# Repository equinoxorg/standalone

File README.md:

#Standalone Designs

##Hardware
This project includes hardware schematics and board layouts for the standalone batterbox (izuba.box) for e.quinox (www.e.quinox.org).

Cadsoft EAGLE is the tool of choice when designing PCBs

###Contents

The following designs are included in this repository

* [Stand_Alone] : The main PCB board controlling payment and outputs
* [Stand_Alone_Inv_Adapter] : The adapter board used in the commercial unit, allows high power loads such as the inverter to be switched. Also provided 2 extra USB outputs and fan contol. Connects the the main boards inverter adapter connector.

##Software

This project includes PIC microcontroller software for the standalone batterbox (izuba.box) for e.quinox (www.e.quinox.org).

The project is MPLAB v1.20. The compiler is the Hi-Tech PIC18 v9.80 Lite C compiler

###Contents

The following designs are included in this repository

* [Stand_Alone] : The main firmware for the standalone units

###Notes
The unlock_code.c file has been deliberatly exluded as it would allow misuse of the payment system. If this is a problem please contact e.quinox.org

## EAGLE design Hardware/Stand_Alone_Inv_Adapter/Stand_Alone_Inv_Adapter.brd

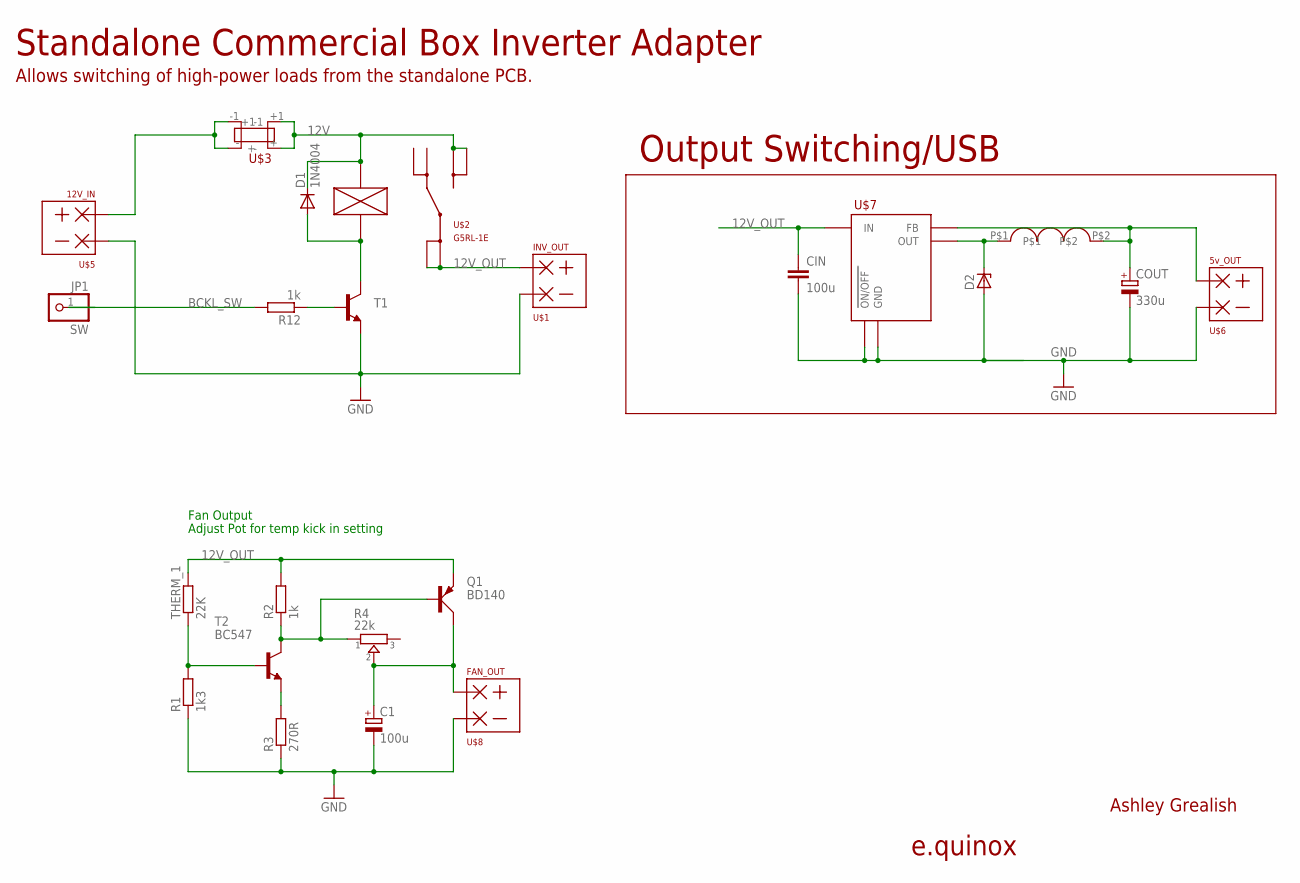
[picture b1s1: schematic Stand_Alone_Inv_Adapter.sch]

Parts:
C1: 100u; B45181B
CIN: 100u; C2.5-2
COUT: 330u; B45181D
D1: 1N4004; DO41-10
D2: ZENER-DIODEDO41Z10; DO41Z10
JP1: SW; 1X01
Q1: BD140; TO126AV
R1: 1k3; 0207/10
R2: 1k; 0207/10
R3: 270R; 0207/10
R4: 22k; TRIMMER_3362P
R12: 1k; RTH025W
T1: BC546-NPN-TO92-CBE; TO92-CBE
T2: BC547; TO92
THERM_1: 22K; 0204/7
U$1: INV_OUT; TERMINAL_2WAY
U$2: G5RL-1E
U$3: EQBX_FUSEEQBX_FUSE; EQBX_FUSE
U$4: EQBX_INDUCTOR2; INDUCTOR
U$5: 12V_IN; TERMINAL_2WAY
U$6: 5v_OUT; TERMINAL_2WAY
U$7: LM2575; TO220-5
U$8: FAN_OUT; TERMINAL_2WAY

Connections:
12V: D1.C, U$2.COIL+, U$2.NO@1 (NO), U$2.NO@2 (NO), U$3.+, U$3.+1
12V_OUT: CIN.1, Q1.E, R2.2, THERM_1.2, U$1.P$1, U$2.COM@1 (COM), U$2.COM@2 (COM), U$7.P$1 (IN)
BCKL_SW: JP1.1, R12.2
GND: C1.-, CIN.2, COUT.-, D2.A, R1.1, R3.1, T1.E, U$1.P$2, U$5.P$2, U$6.P$2, U$7.P$3 (GND), U$7.P$5 (ON/OFF), U$8.P$2
unnamed: D1.A, T1.C, U$2.COIL-
unnamed: R12.1, T1.B
unnamed: U$3.-, U$3.-1, U$5.P$1
unnamed: R1.2, T2.2 (B), THERM_1.1
unnamed: Q1.B, R2.1, R4.1, T2.3 (C)
unnamed: R3.2, T2.1 (E)
unnamed: C1.+, Q1.C, R4.2, U$8.P$1
unnamed: COUT.+, U$4.P$2, U$6.P$1, U$7.P$4 (FB)
unnamed: D2.C, U$4.P$1, U$7.P$2 (OUT)

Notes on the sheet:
e.quinox
Ashley Grealish
Standalone Commercial Box Inverter Adapter
Allows switching of high-power loads from the standalone PCB.
Output Switching/USB
Fan Output
Adjust Pot for temp kick in setting

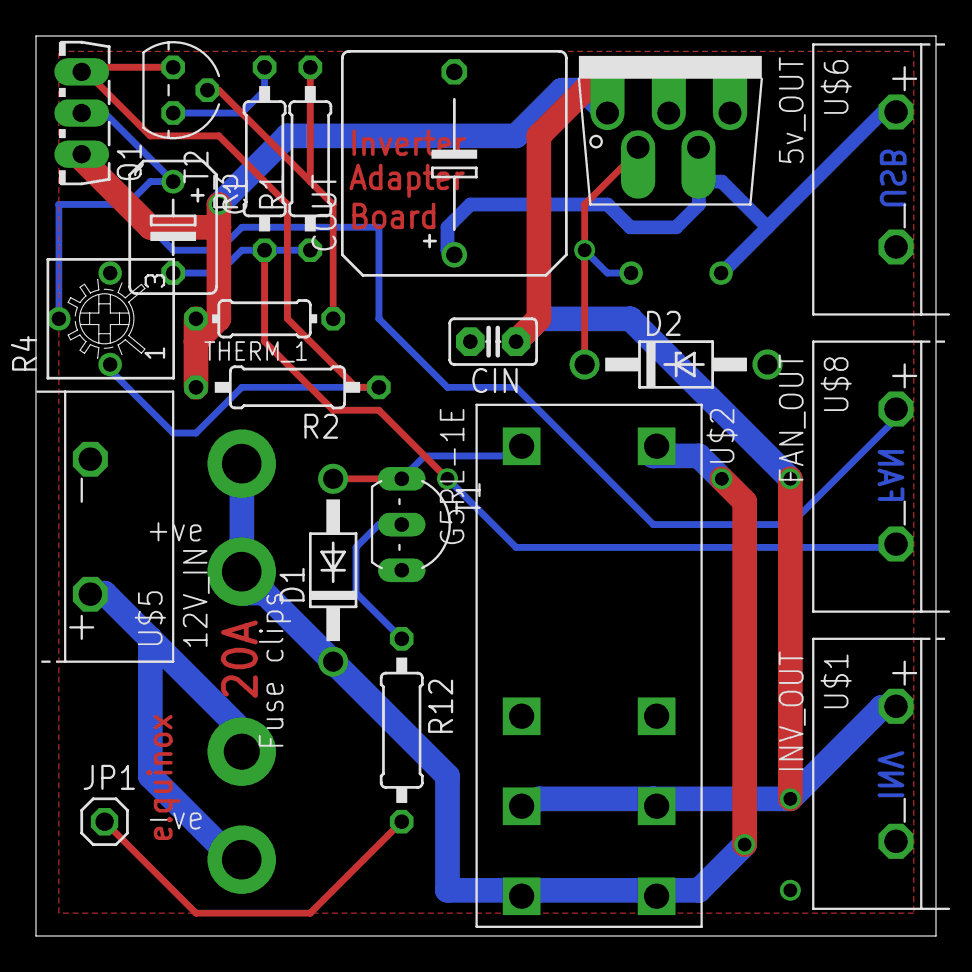
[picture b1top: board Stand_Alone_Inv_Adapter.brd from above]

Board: 2 copper layers, 50.0 x 50.0 mm, 23 parts (0 on the bottom side), 13 nets.

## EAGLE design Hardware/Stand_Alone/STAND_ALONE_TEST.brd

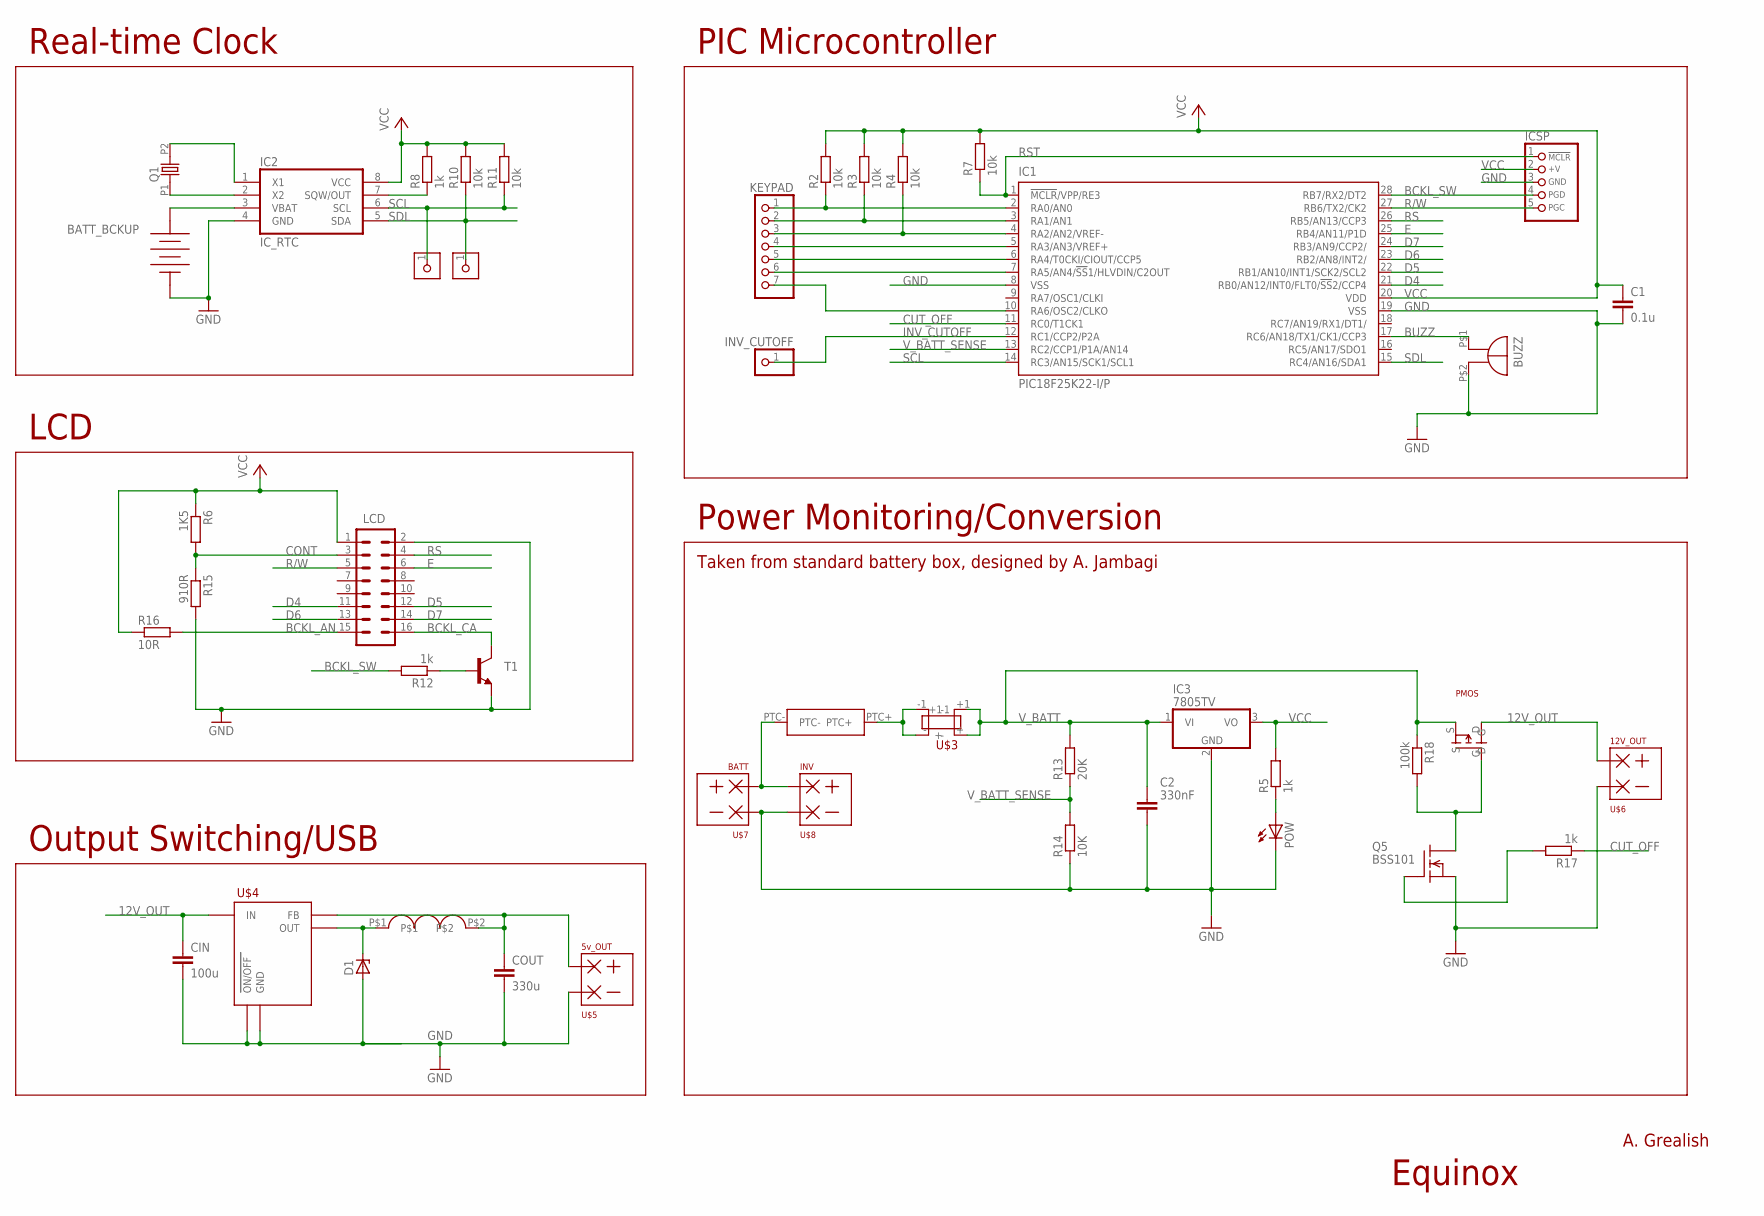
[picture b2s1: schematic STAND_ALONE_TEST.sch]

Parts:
BATT_BCKUP: RENATA_COIN_CELL; PANASONIC_CR2032_1298246
BUZZ: BUZZ_14MM; 14MM_5M_PINS
C1: 0.1u; CAP-PTH-SMALL2
C2: 330nF; C0.1PTH
CIN: 100u; C2.5-2
COUT: 330u; C2.5-2
D1: ZENER-DIODEDO41Z10; DO41Z10
IC1: PIC18F25K22-I/P; DIP28
IC2: IC_RTC; DIP8
IC3: 7805TV; TO220V
ICSP: CON_HEADER_PRG_PIC_ICSPA; HEADER_PRG_1X05
INV_CUTOFF: PINHD-1X1; 1X01
KEYPAD: PINHD-1X7; 1X07
LCD: M08X2-SHROUDED_LOCK; 2X8-SHROUDED_LOCK
PMOS: PMOS; NMOS_IPAK
POW: LED5MM
Q1: OSC-XTALTC-26; TC-26
Q5: BSS101; TO92
R2, R3, R4, R7, R10, R11: 10k; RTH025W
R5, R8, R12, R17: 1k; RTH025W
R6: 1K5; RTH025W
R13: 20K; RTH025W
R14: 10K; RTH025W
R15: 910R; RTH025W
R16: 10R; RTH025W
R18: 100k; RTH025W
T1: BC546-NPN-TO92-CBE; TO92-CBE
TP_SCL: CON_HEADER_1X01-PTH; M1X1
TP_SDL: CON_HEADER_1X01-PTH; M1X1
U$1: EQBX_INDUCTOR2; INDUCTOR
U$2: EQBX_PTCEQBX_PTC; EQBX_PTC
U$3: EQBX_FUSEEQBX_FUSE; EQBX_FUSE
U$4: LM2575; TO220-5
U$5: 5v_OUT; TERMINAL_2WAY
U$6: 12V_OUT; TERMINAL_2WAY
U$7: BATT; TERMINAL_2WAY
U$8: INV; TERMINAL_2WAY

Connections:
12V_OUT: CIN.1, PMOS.D, U$4.P$1 (IN), U$6.P$1
BCKL_AN: LCD.15, R16.2
BCKL_CA: LCD.16, T1.C
BCKL_SW: IC1.28 (RB7/RX2/DT2), ICSP.4 (PGD), R12.2
BUZZ: BUZZ.P$1 (+), IC1.17 (RC6/AN18/TX1/CK1/CCP3)
CONT: LCD.3, R6.2, R15.1
CUT_OFF: IC1.11 (RC0/T1CK1), R17.1
D4: IC1.21 (RB0/AN12/INT0/FLT0/!SS!2/CCP4), LCD.11
D5: IC1.22 (RB1/AN10/INT1/SCK2/SCL2), LCD.12
D6: IC1.23 (RB2/AN8/INT2/), LCD.13
D7: IC1.24 (RB3/AN9/CCP2/), LCD.14
E: IC1.25 (RB4/AN11/P1D), LCD.6
GND: BATT_BCKUP.P- (NEG), BUZZ.P$2 (-), C1.2, C2.2, CIN.2, COUT.2, D1.A, IC1.8 (VSS), IC1.19 (VSS), IC2.4 (GND), IC3.2 (GND), ICSP.3 (GND), LCD.2, POW.K (C), Q5.1 (S), R14.1, R15.2, T1.E, U$4.P$3 (GND), U$4.P$5 (ON/OFF), U$5.P$2, U$6.P$2, U$7.P$2, U$8.P$2
INV_CUTOFF: IC1.12 (RC1/CCP2/P2A), INV_CUTOFF.1
unnamed: PMOS.G, Q5.3 (D), R18.2
unnamed: R12.1, T1.B
unnamed: U$2.PTC-, U$7.P$1, U$8.P$1
unnamed: IC1.2 (RA0/AN0), KEYPAD.1, R2.1
unnamed: IC1.3 (RA1/AN1), KEYPAD.2, R3.1
unnamed: IC1.4 (RA2/AN2/VREF-), KEYPAD.3, R4.1
unnamed: POW.A, R5.1
unnamed: IC1.5 (RA3/AN3/VREF+), KEYPAD.4
unnamed: IC1.6 (RA4/T0CKI/CIOUT/CCP5), KEYPAD.5
unnamed: IC1.7 (RA5/AN4/!SS!1/HLVDIN/C2OUT), KEYPAD.6
unnamed: IC1.10 (RA6/OSC2/CLKO), KEYPAD.7
unnamed: Q5.2 (G), R17.2
unnamed: IC2.2 (X2), Q1.P1 (1)
unnamed: IC2.1 (X1), Q1.P2 (2)
unnamed: IC2.7 (SQW/OUT), R8.1
unnamed: BATT_BCKUP.P+ (POS), IC2.3 (VBAT)
unnamed: COUT.1, U$1.P$2, U$4.P$4 (FB), U$5.P$1
unnamed: U$2.PTC+, U$3.-, U$3.-1
unnamed: D1.C, U$1.P$1, U$4.P$2 (OUT)
R/W: IC1.27 (RB6/TX2/CK2), ICSP.5 (PGC), LCD.5
RS: IC1.26 (RB5/AN13/CCP3), LCD.4
RST: IC1.1 (!MCLR!/VPP/RE3), ICSP.1 (/MCLR), R7.1
SCL: IC1.14 (RC3/AN15/SCK1/SCL1), IC2.6 (SCL), R11.1, TP_SCL.1
SDL: IC1.15 (RC4/AN16/SDA1), IC2.5 (SDA), R10.1, TP_SDL.1
VCC: C1.1, IC1.20 (VDD), IC2.8 (VCC), IC3.3 (VO), ICSP.2 (+V), LCD.1, R2.2, R3.2, R4.2, R5.2, R6.1, R7.2, R8.2, R10.2, R11.2, R16.1
V_BATT: C2.1, IC3.1 (VI), PMOS.S, R13.2, R18.1, U$3.+, U$3.+1
V_BATT_SENSE: IC1.13 (RC2/CCP1/P1A/AN14), R13.1, R14.2

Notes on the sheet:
Power Monitoring/Conversion
PIC Microcontroller
Real-time Clock
LCD
Output Switching/USB
Taken from standard battery box, designed by A. Jambagi
A. Grealish
Equinox

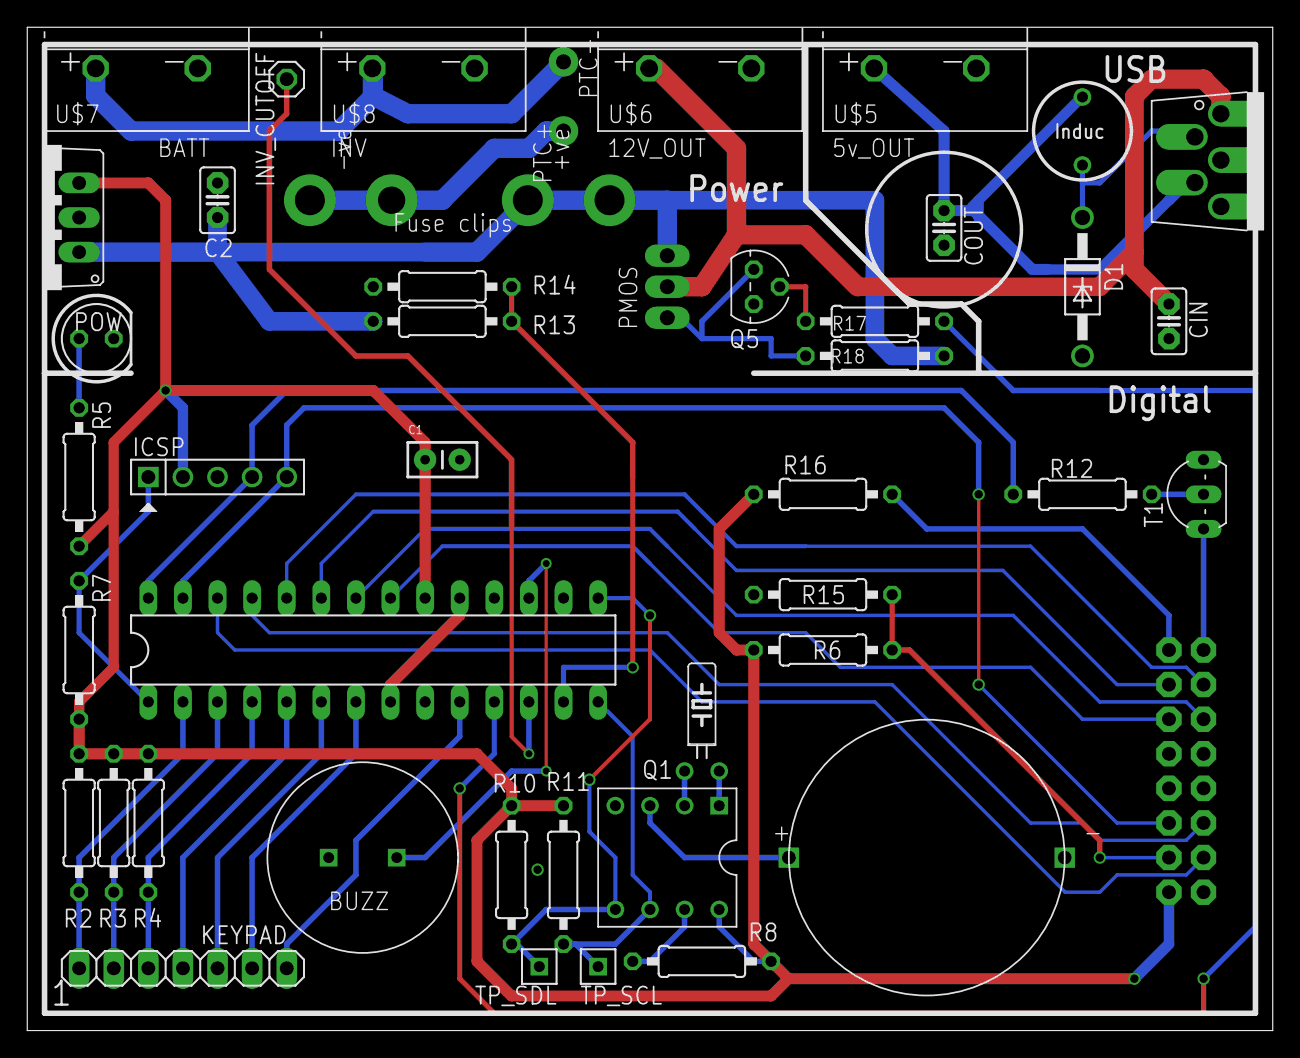
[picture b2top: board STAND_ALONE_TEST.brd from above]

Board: 2 copper layers, 91.4 x 73.7 mm, 45 parts (1 on the bottom side), 41 nets.

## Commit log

2012-10-23 First Commit
    Design files for the first version of the standalone system. Deployed in
    2012 in Minazi
2012-11-14 Add license information
2012-11-14 Update licence information
2012-11-14 Added PDFs of Schematic and board
2013-08-09 Added functionality for setting unlock count
    allows to set unlock count after programming
